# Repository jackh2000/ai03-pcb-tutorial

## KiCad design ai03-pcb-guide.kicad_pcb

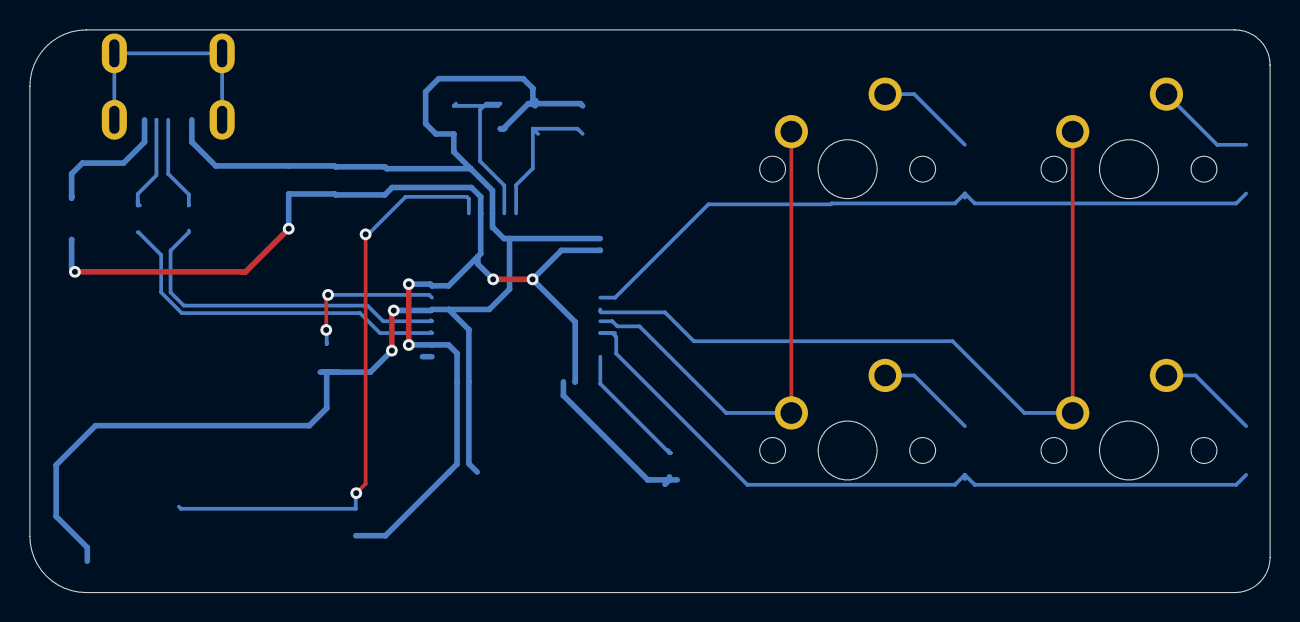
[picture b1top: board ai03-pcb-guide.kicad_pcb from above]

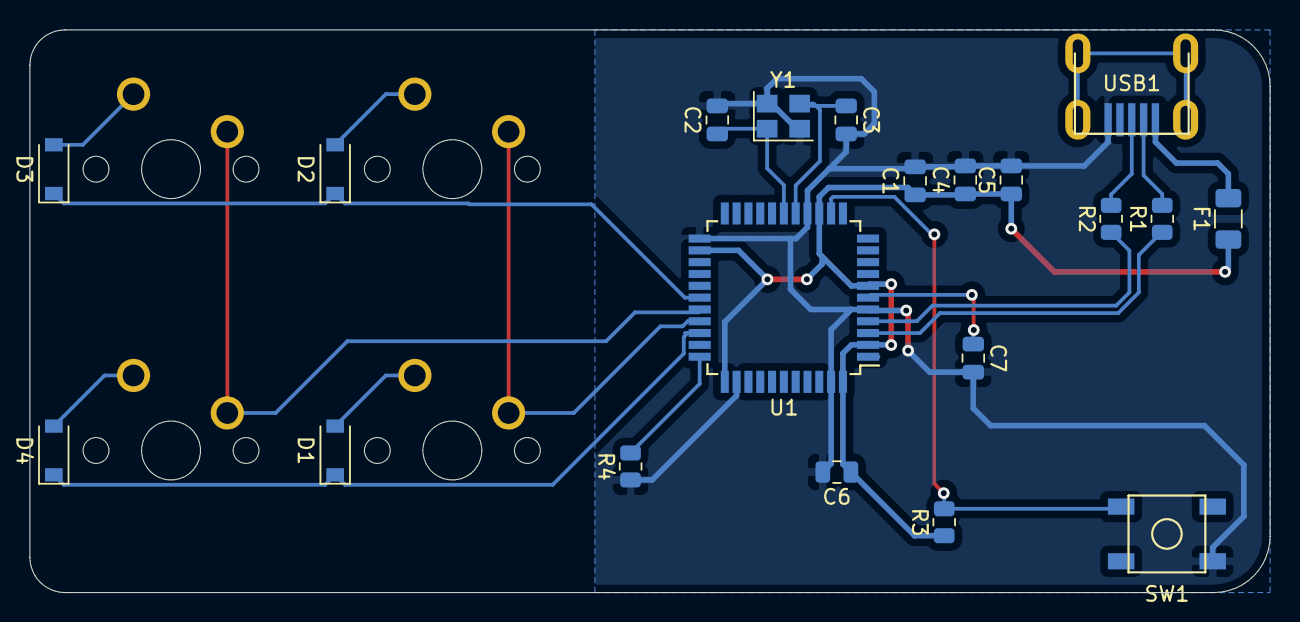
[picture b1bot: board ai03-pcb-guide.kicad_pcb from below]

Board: 2 copper layers, 84.0 x 38.1 mm, 24 parts (20 on the bottom side), 20 nets.

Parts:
C1, C4, C5: 0.1uF; C_0805_2012Metric
C2, C3: 22pF; C_0805_2012Metric
C6: 10uF; C_0805_2012Metric
C7: 1uF; C_0805_2012Metric
D1, D2, D3, D4: D_Small; D_SOD-123
F1: 500mA; Fuse_1206_3216Metric
MX1, MX2, MX3, MX4: MX-NoLED; MXOnly-1U-NoLED
R1, R2: 22Ohms; R_0805_2012Metric
R3, R4: 10kOhms; R_0805_2012Metric
SW1: SW_Push; SKQG-1155865
U1: ATmega32U4-AU; TQFP-44_10x10mm_P0.8mm
USB1: Molex-0548190589
Y1: 16MHz; Crystal_SMD_3225-4Pin_3.2x2.5mm

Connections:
+5V: C1.1, C4.1, C5.1, C6.1, F1.1, R3.1, U1.2, U1.7, U1.14, U1.24, U1.34, U1.44
COL0: MX1.1, MX2.1, U1.30
COL1: MX3.1, MX4.1, U1.29
D+: R2.2, USB1.3
D-: R1.2, USB1.4
GND: C1.2, C2.2, C3.2, C4.2, C5.2, C6.2, C7.2, R4.1, SW1.1, U1.5, U1.15, U1.23, U1.35, U1.43, USB1.1, Y1.2, Y1.4
unnamed: C2.1, U1.17, Y1.1
unnamed: C3.1, U1.16, Y1.3
unnamed: C7.1, U1.6
unnamed: D1.2, MX1.2
unnamed: D2.2, MX2.2
unnamed: D3.2, MX3.2
unnamed: D4.2, MX4.2
unnamed: R1.1, U1.3
unnamed: R2.1, U1.4
unnamed: R3.2, SW1.2, U1.13
unnamed: R4.2, U1.33
ROW0: D2.1, D3.1, U1.28
ROW1: D1.1, D4.1, U1.31
VCC: F1.2, USB1.5

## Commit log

2020-11-16 starter files
2020-11-16 add submodules
2020-11-16 added project specific libraries
2020-11-16 completed .sch file w 2x2 macro matrix
2020-11-16 finished .sch and started to re-arrange PCB
2020-11-23 finished PCB compnent placements and routing
2020-11-23 added ground fill, black soldermask, micro usb error still persists
2020-11-23 added missing traces
2020-11-23 more trace fixes
2020-11-24 redid pcb layout and routing
